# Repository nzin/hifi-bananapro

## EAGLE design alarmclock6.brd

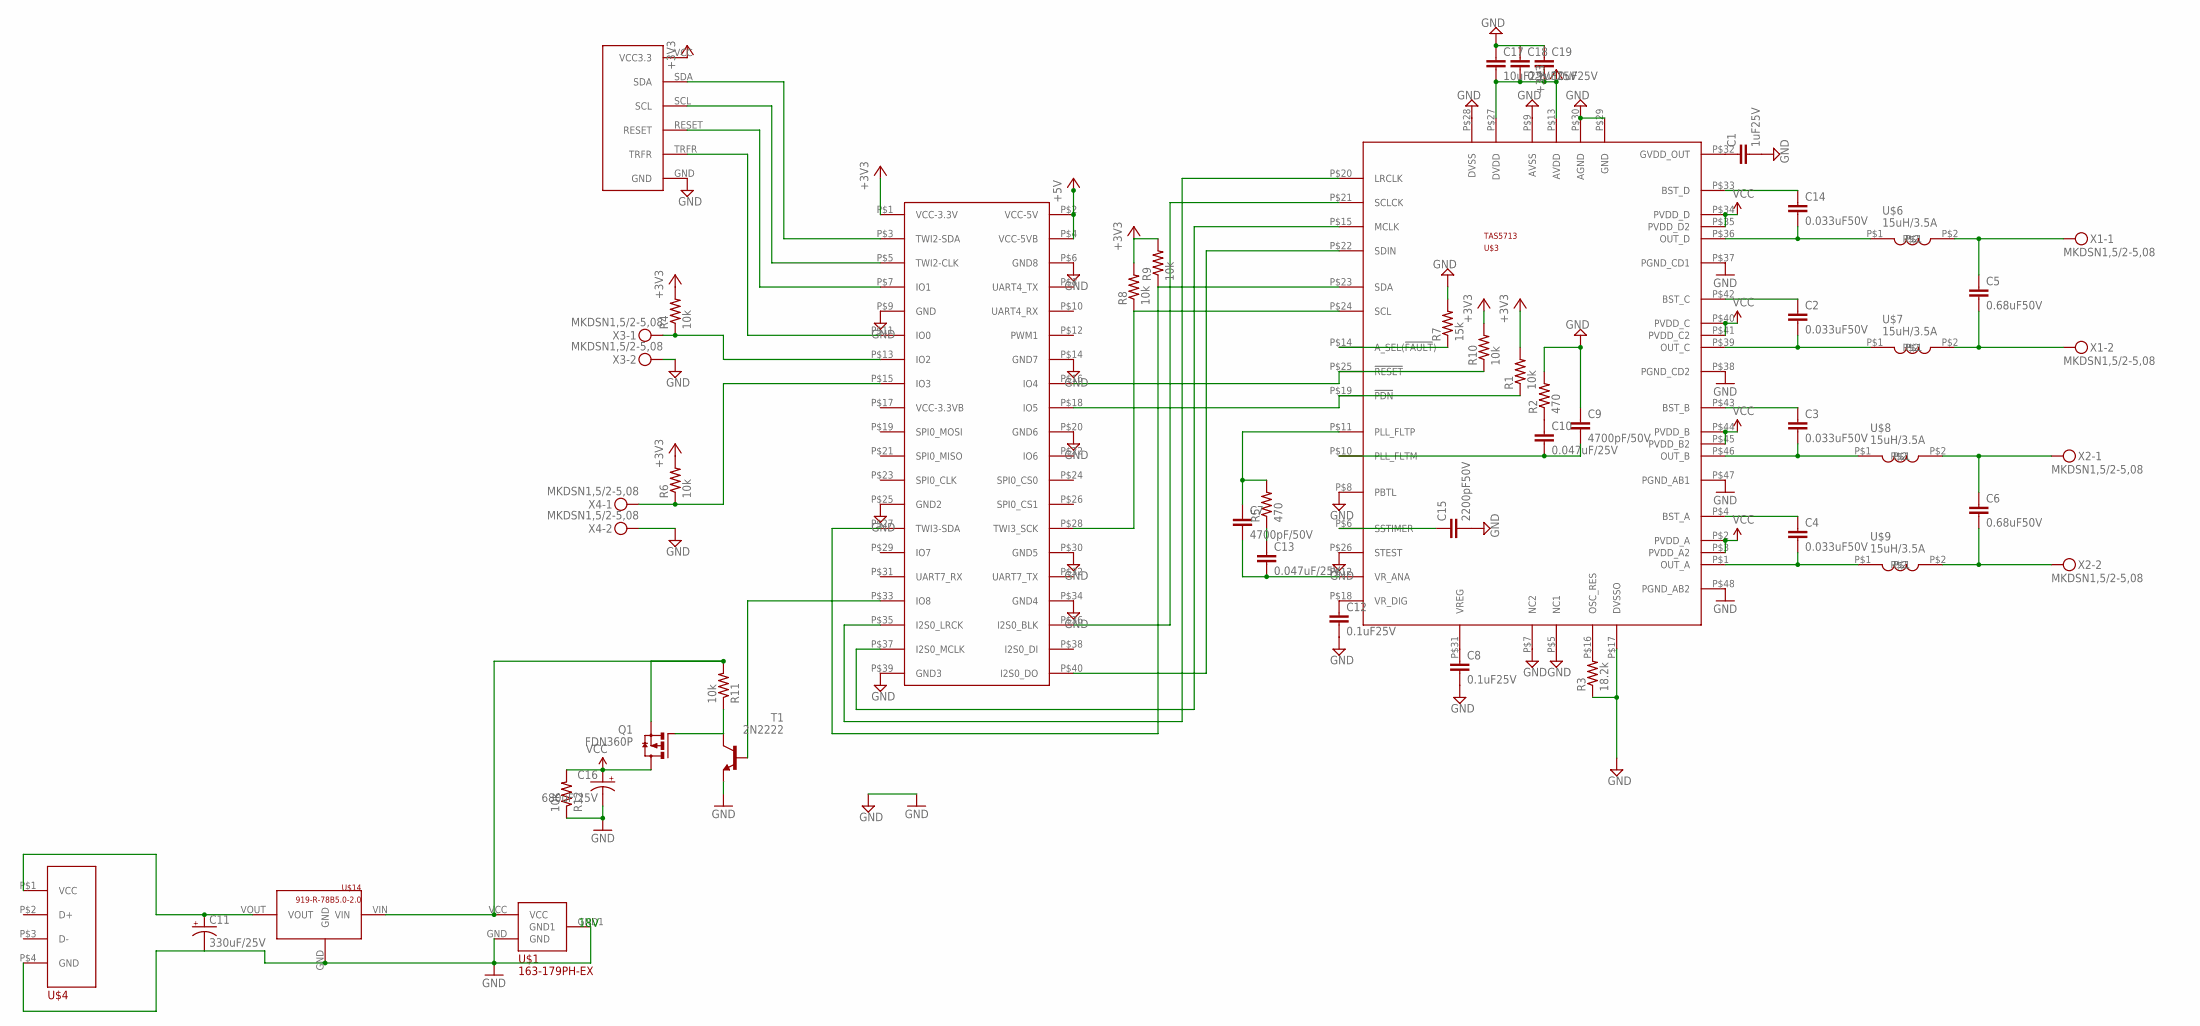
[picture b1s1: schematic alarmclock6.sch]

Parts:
C1: 1uF25V; 0603-CAP
C2, C3, C4, C14: 0.033uF50V; 0603-CAP
C5, C6: 0.68uF50V; 0603-CAP
C7, C9: 4700pF/50V; 0603-CAP
C8, C12, C18: 0.1uF25V; 0603-CAP
C10, C13: 0.047uF/25V; 0603-CAP
C11: 330uF/25V; CPOL-RADIAL-10UF-25V
C15: 2200pF50V; 0603-CAP
C16: 680uF/25V; CPOL-RADIAL-10UF-25V
C17, C19: 10uF25V; 0603-CAP
Q1: FDN360P; SUPER-SOT3
R1, R4, R6, R8, R9, R10, R11, R12: 10k; 0603-RES
R2, R5: 470; 0603-RES
R3: 18.2k; 0603-RES
R7: 15k; 0603-RES
T1: 2N2222; TO18
U$1: 163-179PH-EX; 163-179PH-EX_DIM
U$3: TAS5713; TAS5713_DIM
U$4: USB_TYPEA_CONNECTOR; USB_DIM
U$5: BANANAPRO-CON6; BANANAPRO-CON6_DIM
U$6, U$7, U$8, U$9: 15uH/3.5A; MSS1260_DIM
U$10: SKYWRITER; SKYWRITER_DIM
U$14: 919-R-78B5.0-2.0; 919-R-78B5.0-2.0_DIM
X1, X2, X3, X4: MKDSN1,5/2-5,08

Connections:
+3V3: C17.2, C18.2, C19.2, R1.2, R4.2, R6.2, R8.2, R9.2, R10.2, U$3.P$13 (AVDD), U$3.P$27 (DVDD), U$5.P$1 (VCC-3.3V), U$10.VCC (VCC3.3)
+5V: U$5.P$2 (VCC-5V), U$5.P$4 (VCC-5VB)
GND: C1.2, C8.2, C9.1, C11.2 (-), C12.2, C15.2, C16.2 (-), C17.1, C18.1, C19.1, R2.2, R3.1, R7.2, R12.1, T1.1 (E), U$1.GND, U$1.GND1, U$3.P$5 (NC1), U$3.P$7 (NC2), U$3.P$8 (PBTL), U$3.P$9 (AVSS), U$3.P$17 (DVSSO), U$3.P$26 (STEST), U$3.P$28 (DVSS), U$3.P$29 (GND), U$3.P$30 (AGND), U$3.P$37 (PGND_CD1), U$3.P$38 (PGND_CD2), U$3.P$47 (PGND_AB1), U$3.P$48 (PGND_AB2), U$4.P$4 (GND), U$5.P$6 (GND8), U$5.P$9 (GND), U$5.P$14 (GND7), U$5.P$20 (GND6), U$5.P$25 (GND2), U$5.P$30 (GND5), U$5.P$34 (GND4), U$5.P$39 (GND3), U$10.GND, U$14.GND, X3.2, X4.2
unnamed: U$3.P$22 (SDIN), U$5.P$40 (I2S0_DO)
unnamed: U$3.P$15 (MCLK), U$5.P$37 (I2S0_MCLK)
unnamed: C11.1 (+), U$4.P$1 (VCC), U$14.VOUT
unnamed: U$3.P$20 (LRCLK), U$5.P$35 (I2S0_LRCK)
unnamed: U$3.P$21 (SCLCK), U$5.P$36 (I2S0_BLK)
unnamed: R6.1, U$5.P$15 (IO3), X4.1
unnamed: R3.2, U$3.P$16 (OSC_RES)
unnamed: R4.1, U$5.P$13 (IO2), X3.1
unnamed: C6.1, U$8.P$2, X2.1
unnamed: C14.2, U$3.P$36 (OUT_D), U$6.P$1
unnamed: C14.1, U$3.P$33 (BST_D)
unnamed: C4.1, U$3.P$4 (BST_A)
unnamed: C4.2, U$3.P$1 (OUT_A), U$9.P$1
unnamed: C3.2, U$3.P$46 (OUT_B), U$8.P$1
unnamed: C3.1, U$3.P$43 (BST_B)
unnamed: C2.2, U$3.P$39 (OUT_C), U$7.P$1
unnamed: C2.1, U$3.P$42 (BST_C)
unnamed: C6.2, U$9.P$2, X2.2
unnamed: C5.2, U$7.P$2, X1.2
unnamed: C5.1, U$6.P$2, X1.1
unnamed: C7.1, R5.2, U$3.P$11 (PLL_FLTP)
unnamed: C7.2, C13.2, U$3.P$12 (VR_ANA)
unnamed: C9.2, C10.2, U$3.P$10 (PLL_FLTM)
unnamed: C13.1, R5.1
unnamed: C10.1, R2.1
unnamed: C8.1, U$3.P$31 (VREG)
unnamed: C12.1, U$3.P$18 (VR_DIG)
unnamed: R1.1, U$3.P$19 (!PDN!), U$5.P$18 (IO5)
unnamed: U$5.P$3 (TWI2-SDA), U$10.SDA
unnamed: U$5.P$5 (TWI2-CLK), U$10.SCL
unnamed: U$5.P$7 (IO1), U$10.RESET
unnamed: U$5.P$11 (IO0), U$10.TRFR
unnamed: R7.1, U$3.P$14 (A_SEL(!FAULT!))
unnamed: R9.1, U$3.P$23 (SDA), U$5.P$27 (TWI3-SDA)
unnamed: R8.1, U$3.P$24 (SCL), U$5.P$28 (TWI3_SCK)
unnamed: R10.1, U$3.P$25 (!RESET!), U$5.P$16 (IO4)
unnamed: C1.1, U$3.P$32 (GVDD_OUT)
unnamed: C15.1, U$3.P$6 (SSTIMER)
unnamed: T1.2 (B), U$5.P$33 (IO8)
unnamed: Q1.1 (G), R11.1, T1.3 (C)
unnamed: Q1.2 (S), R11.2, U$1.VCC, U$14.VIN
VCC: C16.1 (+), Q1.3 (D), R12.2, U$3.P$2 (PVDD_A), U$3.P$3 (PVDD_A2), U$3.P$34 (PVDD_D), U$3.P$35 (PVDD_D2), U$3.P$40 (PVDD_C), U$3.P$41 (PVDD_C2), U$3.P$44 (PVDD_B), U$3.P$45 (PVDD_B2)

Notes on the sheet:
18V

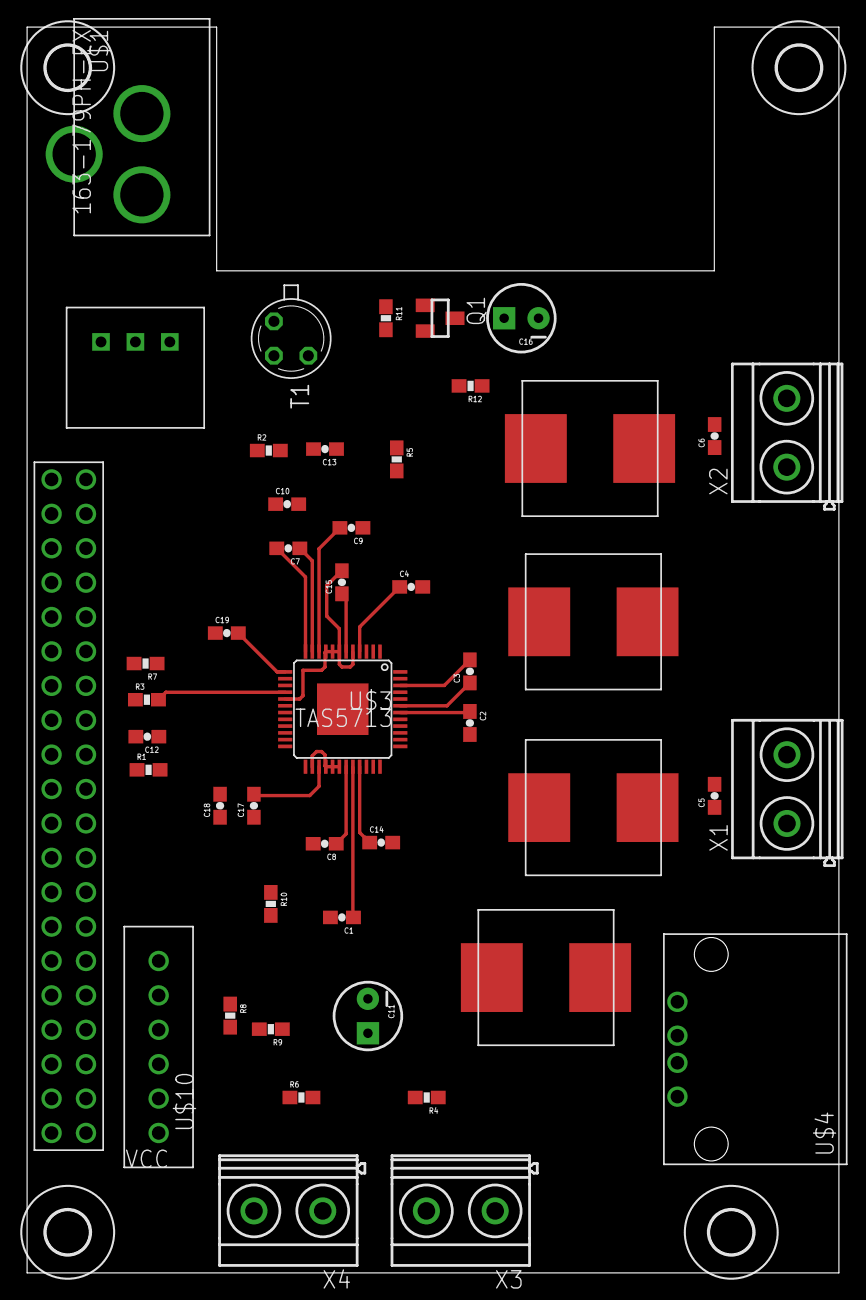
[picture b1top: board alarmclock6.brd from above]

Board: 2 copper layers, 60.0 x 92.0 mm, 51 parts (0 on the bottom side), 45 nets.

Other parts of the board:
U$11, U$12, U$13, U$15: 3,2

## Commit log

2016-09-17 route 100%
2016-09-17 !00% routable
2016-09-17 - separate gnd from 18v stage and 3.3v stage - add 2 gpio as terminal block (2 external push button) - complete the bom
2016-09-17 -add the 10k smd for the push button
2016-09-17 put the 40 pin headers in the correct direction
2016-09-17 alarmclock.sch is too old
2016-09-17 Revert "alarmclock.sch is too old"
    This reverts commit 8a25966ad4365e2754a0be729f3aaea1cfe3d248.
2016-09-18 add extension to the skywriter (https://www.modmypi.com/raspberry-pi/breakout-boards/pimoroni/pimoroni-skywriter)
2016-09-25 i forgot to put the TI chip!
2016-10-07 new board
2016-10-30 - 2 bugfix: orientation of dc-dc + TAS pin SEL must not be to ground - remove via under the TAS chip
2016-10-30 move the capa
2016-10-30 recompute
2016-10-30 add datasheet of the TAS chip
2016-10-30 update mouser library
2016-12-23 new schema with i2c with pullup
2016-12-23 fully routed
2016-12-23 add a reset pin
2017-01-13 bugfix: !reset! not connect directly to vcc
2017-01-14 new board with RESET and PDN accessible via GPIO
2017-02-01 add new capa 2200pf
2017-02-01 change ref for 2200pf
2017-03-04 new schema
2017-03-04 add a R10k resistor to flush the capa
2017-03-04 update bom
2017-10-29 new decoupling capa
2017-12-25 replace the DC-DC converter to a 2A (instead of 400mA)
2017-12-25 bugfix on DC-DC converter

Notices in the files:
parts and their libraries:
SparkFun-Passives: Licensing: Creative Commons ShareAlike 4.0 International - https://creativecommons.org/licenses/by-sa/4.0
